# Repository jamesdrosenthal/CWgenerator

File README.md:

# CWgenerator
CW Generator design files (HW and SW)

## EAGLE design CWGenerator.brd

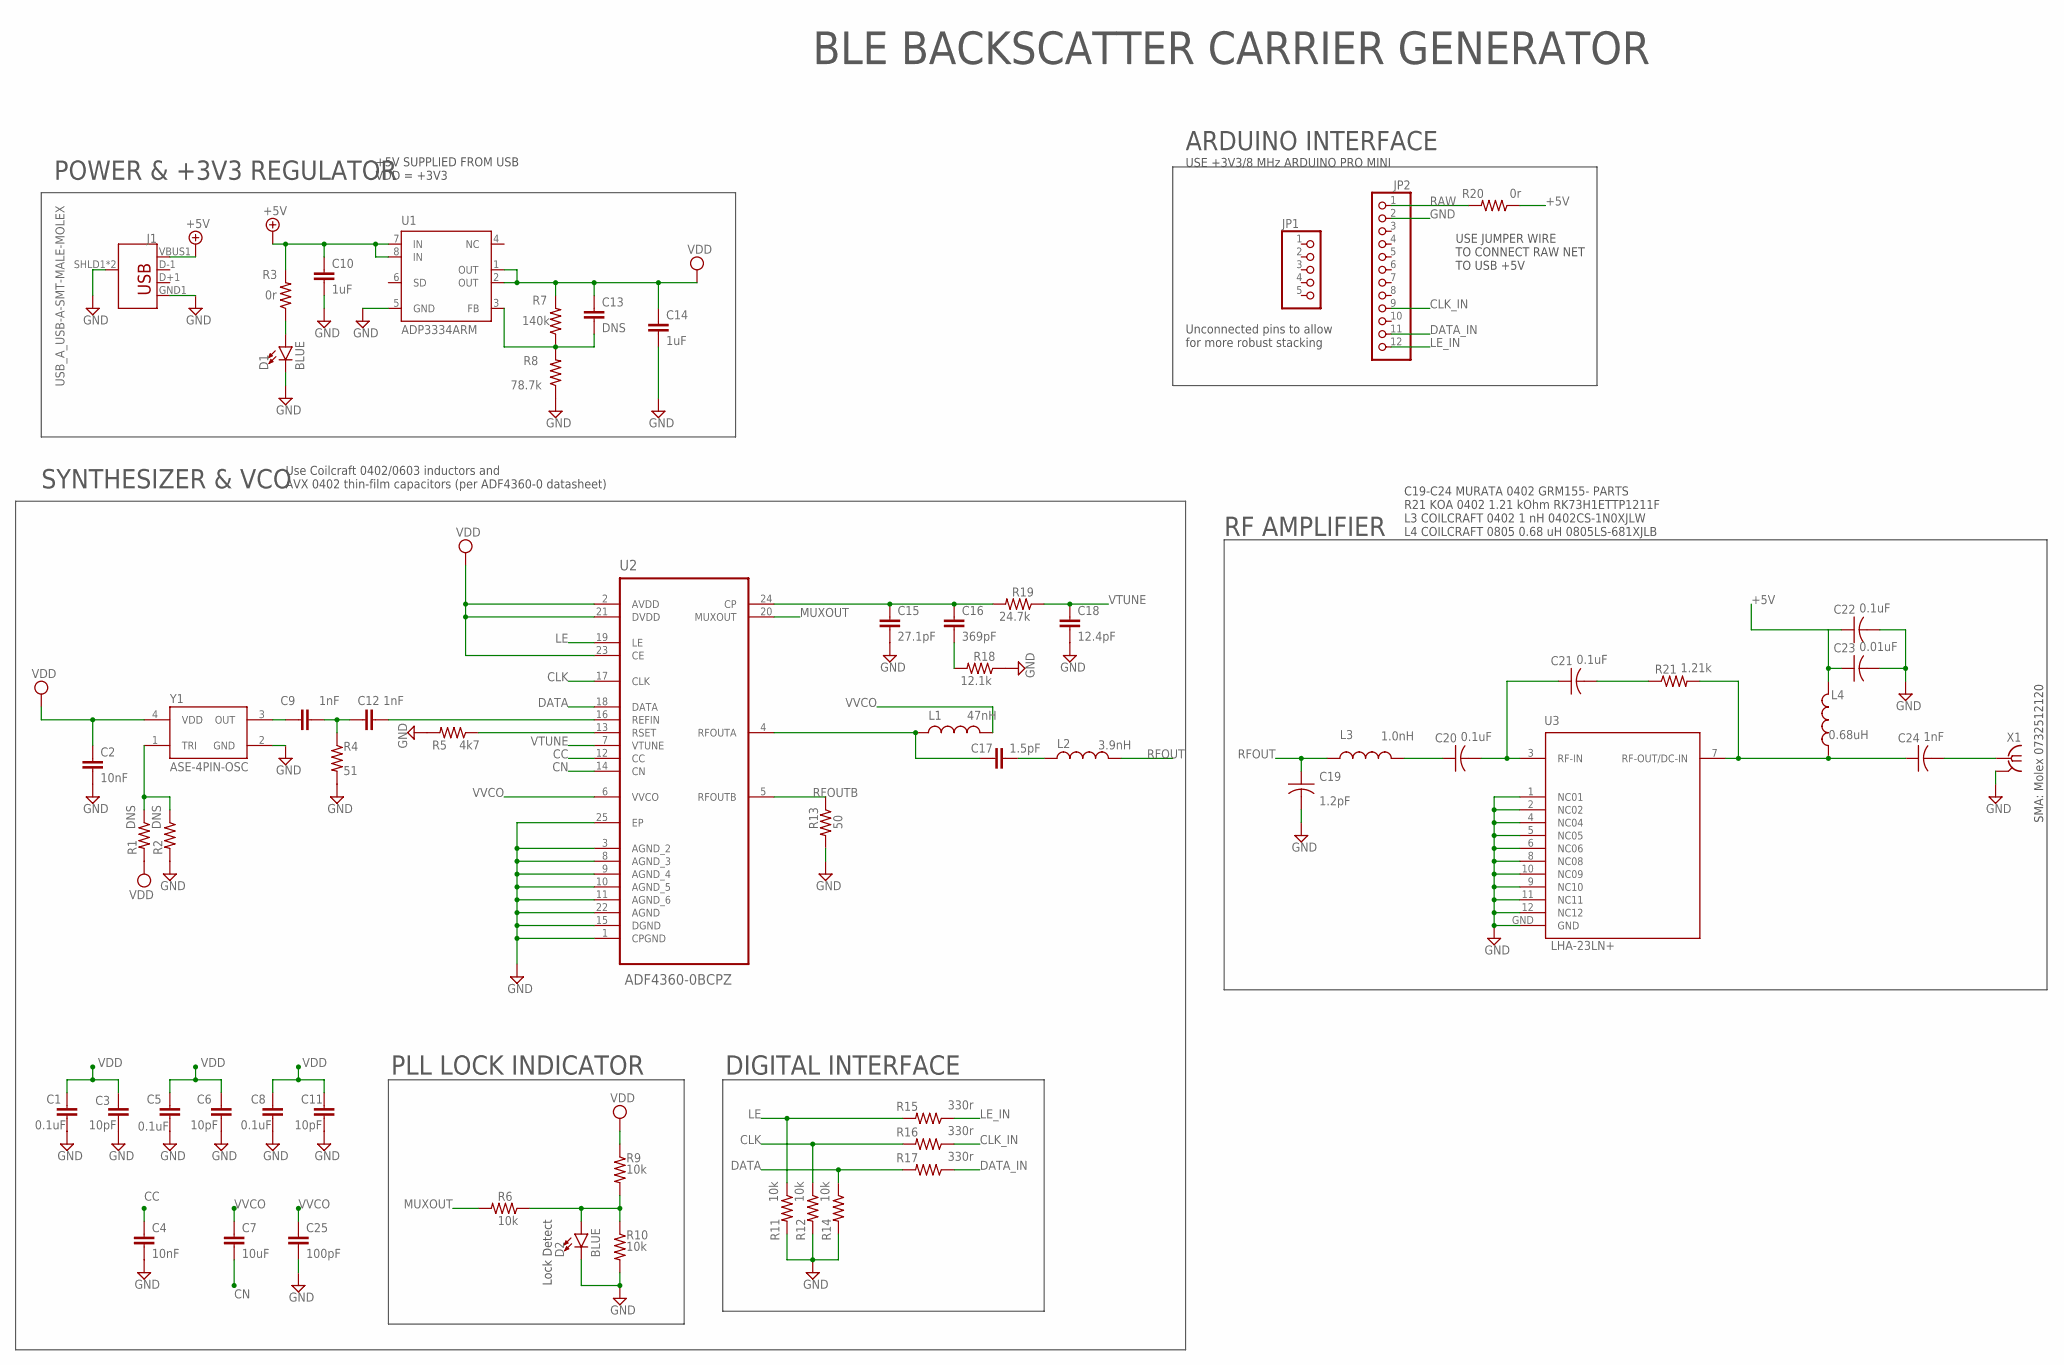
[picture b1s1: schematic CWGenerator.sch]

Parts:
C1, C5, C8, C20, C21, C22: 0.1uF; C0402
C2, C4: 10nF; C0402
C3, C6, C11: 10pF; C0402
C7: 10uF; C0402
C9, C12, C24: 1nF; C0402
C10, C14: 1uF; C0402
C13: DNS; C0402
C15: 27.1pF; C0402
C16: 369pF; C0402
C17: 1.5pF; C0402
C18: 12.4pF; C0402
C19: 1.2pF; C0402
C23: 0.01uF; C0402
C25: 100pF; C0402
D1, D2: BLUE; LED-0603
J1: USB_A_USB-A-SMT-MALE-MOLEX; USB-A-SMT-MALE-MOLEX
JP1: PINHD-1X5; 1X05
JP2: PINHD-1X12; 1X12
L1: 47nH; C0402
L2: 3.9nH; C0402
L3: 1.0nH; C0402
L4: 0.68uH; R0805
R1, R2: DNS; R0402
R3, R20: 0r; R0402
R4: 51; R0402
R5: 4k7; R0402
R6, R9, R10, R11, R12, R14: 10k; R0402
R7: 140k; R0402
R8: 78.7k; R0402
R13: 50; R0402
R15, R16, R17: 330r; R0402
R18: 12.1k; R0402
R19: 24.7k; R0402
R21: 1.21k; R0402
U1: ADP3334ARM; MSOP08
U2: ADF4360-0BCPZ; QFN50P400X400X100-25N
U3: LHA-23LN+; MCLP
X1: SMA-142-0711-821/826; J502-ND-142-0711-821/826
Y1: ASE-4PIN-OSC; 3.2X2.5MM

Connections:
+5V: C10.1, C22.1, C23.1, J1.VBUS1 (VBUS), L4.2, R3.2, R20.1, U1.7 (IN), U1.8 (IN)
CC: C4.1, U2.12 (CC)
CLK: R12.1, R16.2, U2.17 (CLK)
CLK_IN: JP2.9, R16.1
CN: C7.2, U2.14 (CN)
DATA: R14.1, R17.2, U2.18 (DATA)
DATA_IN: JP2.11, R17.1
GND: C1.2, C2.2, C3.2, C4.2, C5.2, C6.2, C8.2, C10.2, C11.2, C14.2, C15.2, C18.2, C19.2, C22.2, C23.2, C25.2, D1.C, D2.C, J1.GND1 (GND), J1.SHLD1 (SHIELD), J1.SHLD2 (SHIELD), JP2.2, R2.2, R4.2, R5.2, R8.1, R10.2, R11.2, R12.2, R13.2, R14.2, R18.1, U1.5 (GND), U2.1 (CPGND), U2.3 (AGND_2), U2.8 (AGND_3), U2.9 (AGND_4), U2.10 (AGND_5), U2.11 (AGND_6), U2.15 (DGND), U2.22 (AGND), U2.25 (EP), U3.1 (NC01), U3.2 (NC02), U3.4 (NC04), U3.5 (NC05), U3.6 (NC06), U3.8 (NC08), U3.9 (NC10), U3.10 (NC09), U3.11 (NC11), U3.12 (NC12), U3.GND, X1.G@1 (2), X1.G@2 (2), X1.G@3 (2), X1.G@4 (2), Y1.2 (GND)
LE: R11.1, R15.2, U2.19 (LE)
LE_IN: JP2.12, R15.1
MUXOUT: R6.2, U2.20 (MUXOUT)
unnamed: D1.A, R3.1
unnamed: C20.1, L3.2
unnamed: C20.2, C21.1, U3.3 (RF-IN)
unnamed: C21.2, R21.1
unnamed: C24.1, L4.1, R21.2, U3.7 (RF-OUT/DC-IN)
unnamed: C13.2, R7.1, R8.2, U1.3 (FB)
unnamed: R5.1, U2.13 (RSET)
unnamed: C17.2, L2.1
unnamed: C15.1, C16.1, R19.2, U2.24 (CP)
unnamed: C16.2, R18.2
unnamed: C12.2, U2.16 (REFIN)
unnamed: C9.2, C12.1, R4.1
unnamed: D2.A, R6.1, R9.2, R10.1
unnamed: C24.2, X1.1
unnamed: C9.1, Y1.3 (OUT)
unnamed: R1.1, R2.1, Y1.1 (TRI)
RAW: JP2.1, R20.2
RFOUT: C19.1, L2.2, L3.1
RFOUTA: C17.1, L1.1, U2.4 (RFOUTA)
RFOUTB: R13.1, U2.5 (RFOUTB)
VDD: C1.1, C2.1, C3.1, C5.1, C6.1, C8.1, C11.1, C13.1, C14.1, R1.2, R7.2, R9.1, U1.1 (OUT), U1.2 (OUT), U2.2 (AVDD), U2.21 (DVDD), U2.23 (CE), Y1.4 (VDD)
VTUNE: C18.1, R19.1, U2.7 (VTUNE)
VVCO: C7.1, C25.1, L1.2, U2.6 (VVCO)

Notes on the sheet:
BLE BACKSCATTER CARRIER GENERATOR
Use Coilcraft 0402/0603 inductors and AVX 0402 thin-film capacitors (per ADF4360-0 datasheet)
Lock Detect
SYNTHESIZER & VCO
PLL LOCK INDICATOR
DIGITAL INTERFACE
RF AMPLIFIER
C19-C24 MURATA 0402 GRM155- PARTS R21 KOA 0402 1.21 kOhm RK73H1ETTP1211F L3 COILCRAFT 0402 1 nH 0402CS-1N0XJLW L4 COILCRAFT 0805 0.68 uH 0805LS-681XJLB
POWER & +3V3 REGULATOR
+5V SUPPLIED FROM USB VDD = +3V3
ARDUINO INTERFACE
USE +3V3/8 MHz ARDUINO PRO MINI
Unconnected pins to allow for more robust stacking
USE JUMPER WIRE TO CONNECT RAW NET TO USB +5V
SMA: Molex 0732512120

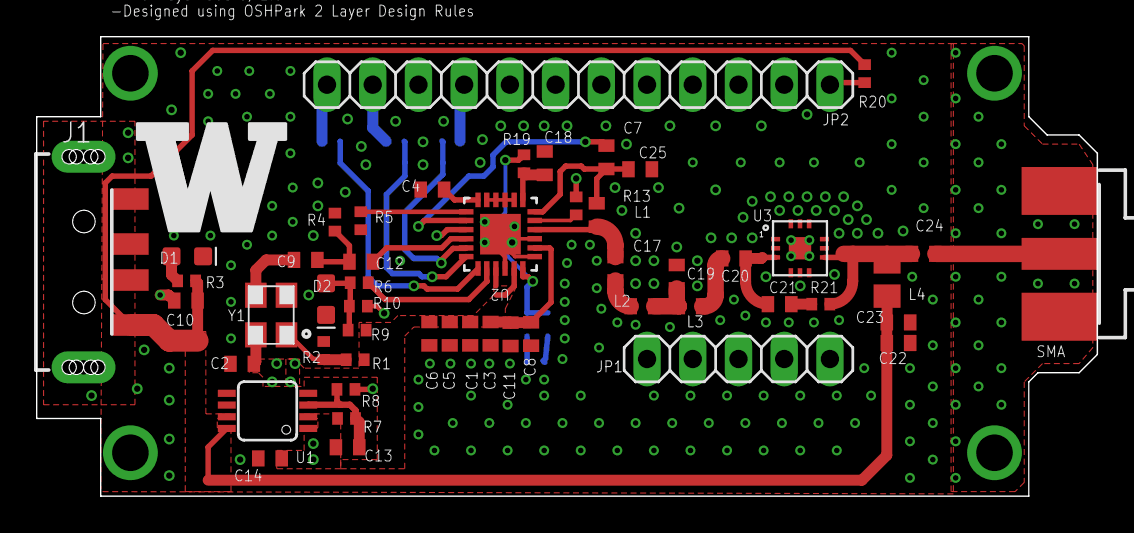
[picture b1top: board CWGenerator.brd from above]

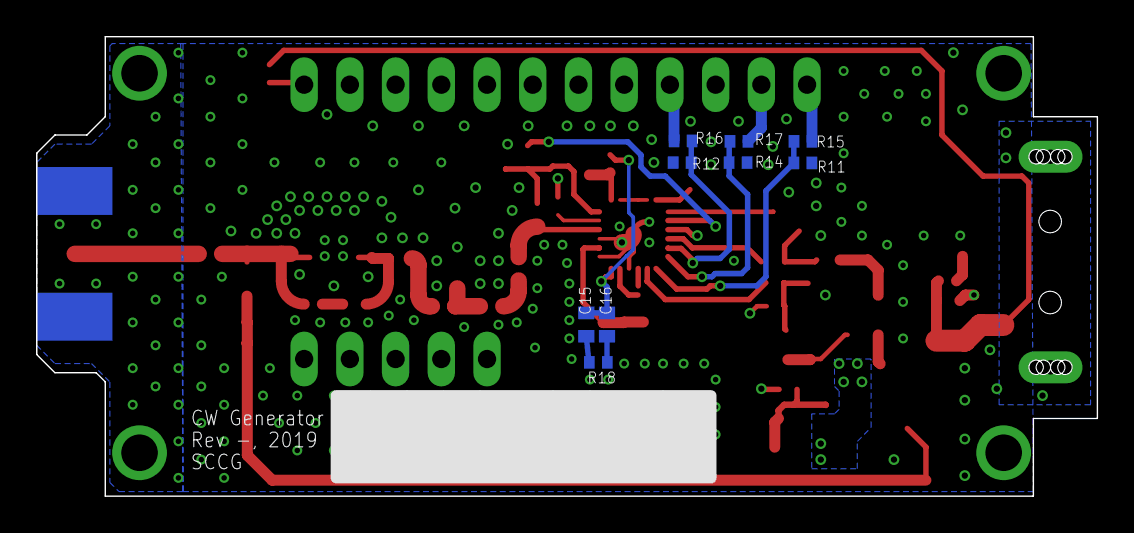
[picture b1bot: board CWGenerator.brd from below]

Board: 2 copper layers, 58.9 x 25.5 mm, 60 parts (9 on the bottom side), 34 nets.

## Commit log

2020-03-26 Add Arduino file
2020-03-26 Add PCB design files

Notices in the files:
parts and their libraries:
SparkFun-LED: Licensing: Creative Commons ShareAlike 4.0 International - https://creativecommons.org/licenses/by-sa/4.0
